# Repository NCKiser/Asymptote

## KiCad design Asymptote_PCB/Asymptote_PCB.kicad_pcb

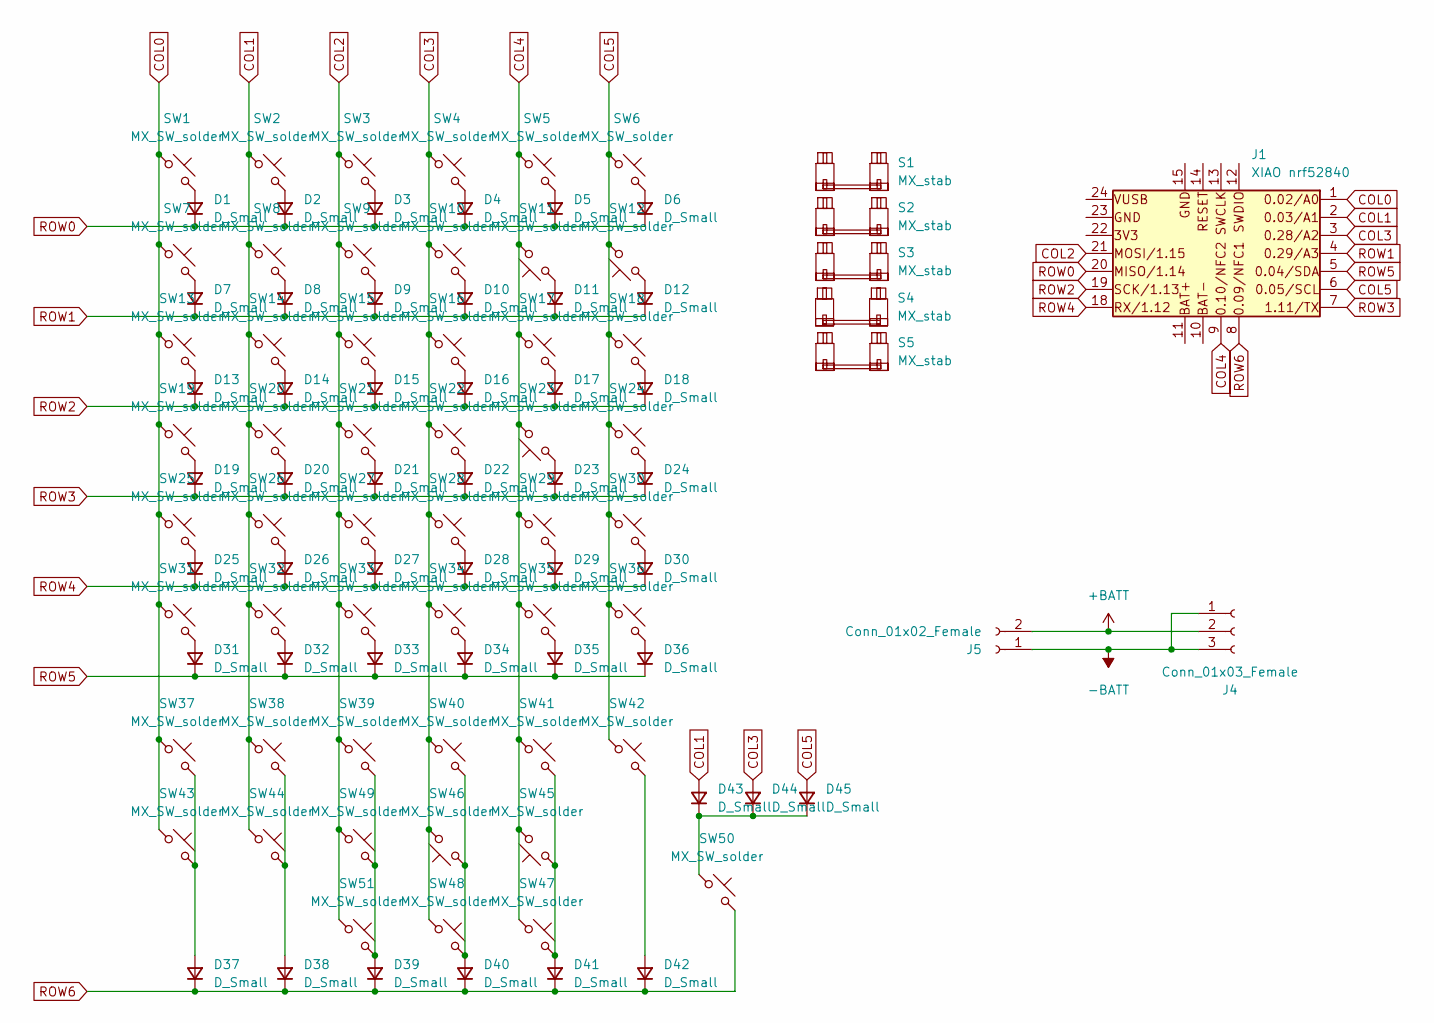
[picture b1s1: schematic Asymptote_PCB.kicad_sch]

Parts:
D1, D2, D3, D4, D5, D6, D7, D8, D9, D10, D11, D12, D13, D14, D15, D16, D17, D18, D19, D20, D21, D22, D23, D24, D25, D26, D27, D28, D29, D30, D31, D32, D33, D34, D35, D36, D37, D38, D39, D40, D41, D42, D43, D44, D45: D_Small; D_A-405_P10.16mm_Horizontal
J1: XIAO nrf52840; XIAO_BLE_NEG
J4: Conn_01x03_Female; JST_PH_S3B-PH-K_1x03_P2.00mm_Horizontal
J5: Conn_01x02_Female; JST_PH_S2B-PH-K_1x02_P2.00mm_Horizontal
S1: MX_stab; STAB_MX_P_2.75u
S2, S3, S4: MX_stab; STAB_MX_P_3u
S5: MX_stab; STAB_MX_P_7u
SW1, SW2, SW3, SW4, SW5, SW6, SW7, SW8, SW9, SW10, SW11, SW14, SW15, SW16, SW17, SW18, SW19, SW20, SW21, SW22, SW23, SW26, SW27, SW28, SW29, SW30, SW31, SW32, SW33, SW34, SW35, SW36, SW37, SW42, SW47, SW48, SW49, SW50, SW51: MX_SW_solder; SW_MX_1u
SW12, SW25, SW39, SW40: MX_SW_solder; SW_MX_1.75u
SW13, SW38, SW41, SW44: MX_SW_solder; SW_MX_1.25u
SW24, SW43, SW45, SW46: MX_SW_solder; SW_MX_1.5u

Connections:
+BATT: J4.2, J5.2
-BATT: J4.1, J4.3, J5.1
COL0: J1.1, SW1.1, SW7.1, SW13.1, SW19.1, SW25.1, SW31.1, SW37.1, SW43.1
COL1: D43.2 (A), J1.2, SW2.1, SW8.1, SW14.1, SW20.1, SW26.1, SW32.1, SW38.1, SW44.1
COL2: J1.21, SW3.1, SW9.1, SW15.1, SW21.1, SW27.1, SW33.1, SW39.1, SW49.1, SW51.1
COL3: D44.2 (A), J1.3, SW4.1, SW10.1, SW16.1, SW22.1, SW28.1, SW34.1, SW40.1, SW46.2, SW48.1
COL4: J1.9, SW5.1, SW11.2, SW17.1, SW23.2, SW29.1, SW35.1, SW41.1, SW45.2, SW47.1
COL5: D45.2 (A), J1.6, SW6.1, SW12.2, SW18.1, SW24.1, SW30.1, SW36.1, SW42.1
unnamed: D1.2 (A), SW1.2
unnamed: D2.2 (A), SW2.2
unnamed: D3.2 (A), SW3.2
unnamed: D4.2 (A), SW4.2
unnamed: D5.2 (A), SW5.2
unnamed: D6.2 (A), SW6.2
unnamed: D7.2 (A), SW7.2
unnamed: D8.2 (A), SW8.2
unnamed: D9.2 (A), SW9.2
unnamed: D10.2 (A), SW10.2
unnamed: D11.2 (A), SW11.1
unnamed: D12.2 (A), SW12.1
unnamed: D13.2 (A), SW13.2
unnamed: D14.2 (A), SW14.2
unnamed: D15.2 (A), SW15.2
unnamed: D16.2 (A), SW16.2
unnamed: D17.2 (A), SW17.2
unnamed: D18.2 (A), SW18.2
unnamed: D19.2 (A), SW19.2
unnamed: D20.2 (A), SW20.2
unnamed: D21.2 (A), SW21.2
unnamed: D22.2 (A), SW22.2
unnamed: D23.2 (A), SW23.1
unnamed: D24.2 (A), SW24.2
unnamed: D25.2 (A), SW25.2
unnamed: D26.2 (A), SW26.2
unnamed: D27.2 (A), SW27.2
unnamed: D28.2 (A), SW28.2
unnamed: D29.2 (A), SW29.2
unnamed: D30.2 (A), SW30.2
unnamed: D31.2 (A), SW31.2
unnamed: D32.2 (A), SW32.2
unnamed: D33.2 (A), SW33.2
unnamed: D34.2 (A), SW34.2
unnamed: D35.2 (A), SW35.2
unnamed: D36.2 (A), SW36.2
unnamed: D37.2 (A), SW37.2, SW43.2
unnamed: D38.2 (A), SW38.2, SW44.2
unnamed: D39.2 (A), SW39.2, SW49.2, SW51.2
unnamed: D40.2 (A), SW40.2, SW46.1, SW48.2
unnamed: D41.2 (A), SW41.2, SW45.1, SW47.2
unnamed: D42.2 (A), SW42.2
unnamed: D43.1 (K), D44.1 (K), D45.1 (K), SW50.1
ROW0: D1.1 (K), D2.1 (K), D3.1 (K), D4.1 (K), D5.1 (K), D6.1 (K), J1.20
ROW1: D7.1 (K), D8.1 (K), D9.1 (K), D10.1 (K), D11.1 (K), D12.1 (K), J1.4
ROW2: D13.1 (K), D14.1 (K), D15.1 (K), D16.1 (K), D17.1 (K), D18.1 (K), J1.19
ROW3: D19.1 (K), D20.1 (K), D21.1 (K), D22.1 (K), D23.1 (K), D24.1 (K), J1.7
ROW4: D25.1 (K), D26.1 (K), D27.1 (K), D28.1 (K), D29.1 (K), D30.1 (K), J1.18
ROW5: D31.1 (K), D32.1 (K), D33.1 (K), D34.1 (K), D35.1 (K), D36.1 (K), J1.5
ROW6: D37.1 (K), D38.1 (K), D39.1 (K), D40.1 (K), D41.1 (K), D42.1 (K), J1.8, SW50.2

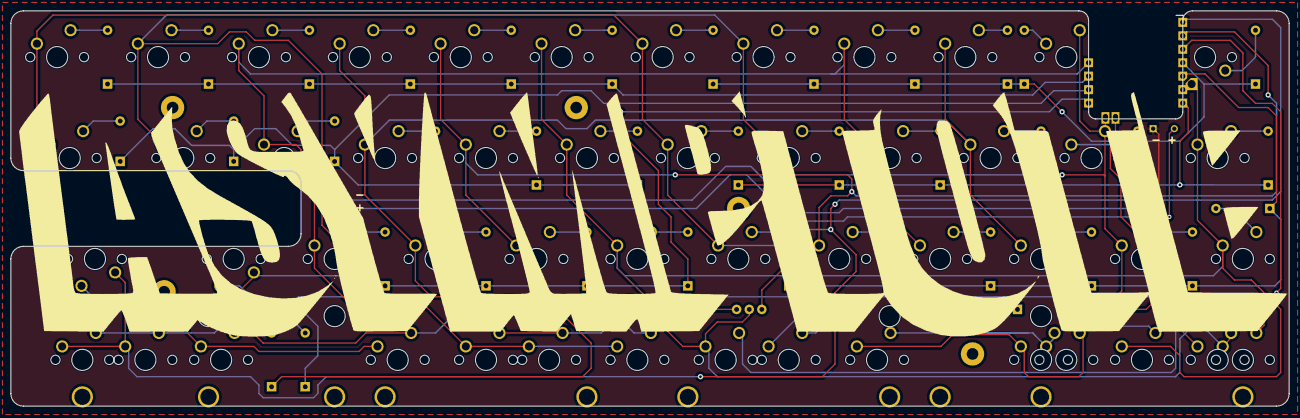
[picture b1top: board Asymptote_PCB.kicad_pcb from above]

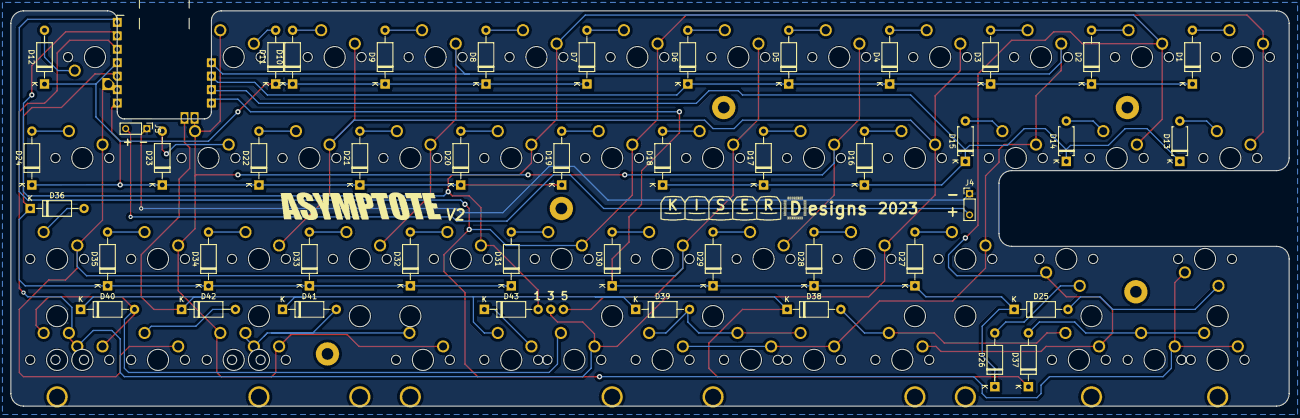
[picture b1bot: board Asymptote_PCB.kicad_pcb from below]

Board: 2 copper layers, 241.2 x 74.6 mm, 105 parts (48 on the bottom side), 58 nets.

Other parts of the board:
H1: MountingHole_Pad; Minivan-reference

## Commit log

2023-02-22 Added plate
2023-03-07 gerbers
2023-05-24 Added 7u stab holes, V2 Gerbers
2023-07-21 Add Campitrayhulliander
2023-07-24 asymplate finished?
2023-07-24 add cutouts
